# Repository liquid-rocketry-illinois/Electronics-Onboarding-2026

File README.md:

# LRI Electronics Onboarding 2026

This repository is still under construction.

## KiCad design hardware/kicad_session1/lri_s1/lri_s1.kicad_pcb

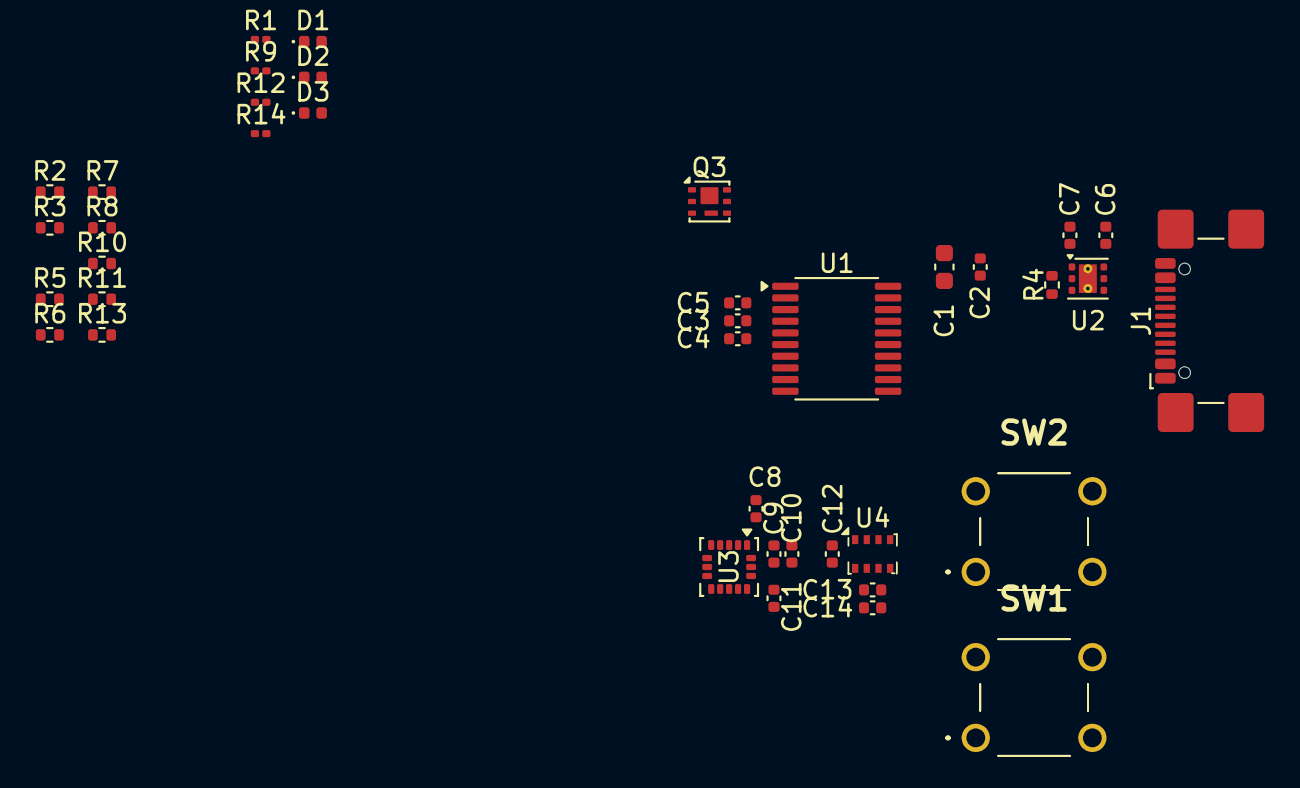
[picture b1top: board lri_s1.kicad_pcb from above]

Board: 2 copper layers, 43 parts (0 on the bottom side), 22 nets, no tracks yet.

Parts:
C1: 4.7u; C_0603_1608Metric
C2, C5, C8, C9, C11, C12, C13: 100n; C_0402_1005Metric
C3, C6, C7: 1u; C_0402_1005Metric
C4: 10n; C_0402_1005Metric
C10, C14: 2.2u; C_0402_1005Metric
D1: GREEN; LED_0402_1005Metric
D2: BLUE; LED_0402_1005Metric
D3: RED; LED_0402_1005Metric
H1, H2, H3, H4: MountingHole; MountingHole_3.2mm_M3
J1: USB_C_Receptacle_USB2.0_16P; USB_C_Receptacle_GCT_USB4110
Q3: CSD17318Q2; Texas_DQK
R1, R9, R12, R14: 10k; R_0201_0603Metric
R2, R3, R4: 5.1k; R_0402_1005Metric
R5, R6, R7: 1k; R_0402_1005Metric
R8, R10, R11, R13: 100; R_0402_1005Metric
SW1, SW2: MJTP1230
U1: STM32F042F6P6; TSSOP-20_4.4x6.5mm_P0.65mm
U2: LP5912-3.3DRV; WSON-6-1EP_2x2mm_P0.65mm_EP1x1.6mm_ThermalVias
U3: ICM-20602; LGA-16_3x3mm_P0.5mm_LayoutBorder3x5y
U4: BMP280; Bosch_LGA-8_2x2.5mm_P0.65mm_ClockwisePinNumbering

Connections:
+3V3: C1.2, C2.2, C3.1, C4.1, C5.2, C7.1, C8.2, C9.2, C10.2, C12.2, C13.2, C14.2, R1.1, R4.1, R5.2, SW1.3 (K), SW1.4 (A), U1.1 (PB8), U1.4 (NRST), U1.5 (VDDA), U1.16 (VDD), U2.1 (OUT), U3.1 (VDDIO), U3.16 (VDD), U4.6 (VDDIO), U4.8 (VDD)
/BMP_~CS: U1.10 (PA4), U4.2 (CSB)
/ICM_~CS: U1.9 (PA3), U3.5 (~CS)
/MCU_LED: R11.2, U1.6 (PA0)
/MCU_PY1: R8.2, R13.2, U1.7 (PA1)
/SPI1_MISO: U1.12 (PA6), U3.4 (SAO/SD0), U4.4 (SCK)
/SPI1_MOSI: U1.11 (PA5), U3.3 (SDA/SDI), U4.3 (SDI)
/SPI1_SCK: U1.13 (PA7), U3.2 (SCL/SPC), U4.5 (SDO)
/USB_D+: J1.A6 (D+), J1.B6 (D+), U1.18 (PA10/PA12)
/USB_D-: J1.A7 (D-), J1.B7 (D-), U1.17 (PA9/PA11)
GND: C1.1, C2.1, C3.2, C4.2, C5.1, C6.2, C7.2, C8.1, C9.1, C10.1, C11.2, C12.1, C13.1, C14.1, D1.1 (K), D2.1 (K), D3.1 (K), J1.A1 (GND), J1.A12 (GND), J1.B1 (GND), J1.B12 (GND), Q3.4 (S), Q3.7 (S), R2.2, R3.2, R9.1, R12.1, R14.1, SW1.1, SW1.2, SW2.1, SW2.2, U1.15 (VSSA), U2.5 (GND), U3.8 (FSYNC), U3.9 (GND), U3.10 (GND), U3.11 (GND), U3.12 (GND), U3.13 (GND), U3.15 (GND), U4.1 (GND), U4.7 (GND)
unnamed: D1.2 (A), R5.1
unnamed: J1.A5 (CC1), R2.1
unnamed: J1.B5 (CC2), R3.1
unnamed: R11.1, R12.2
unnamed: R13.1, R14.2
unnamed: Q3.1 (D), Q3.2 (D), Q3.5 (D), Q3.6 (D), Q3.8 (D), R10.2
unnamed: Q3.3 (G), R8.1, R9.2
unnamed: R1.2, SW2.3 (K), SW2.4 (A)
unnamed: R4.2, U2.3 (PG)
unnamed: C11.1, U3.14 (REGOUT)
VBUS: C6.1, J1.A4 (VBUS), J1.A9 (VBUS), J1.B4 (VBUS), J1.B9 (VBUS), R6.2, R7.2, U2.4 (EN), U2.6 (IN)

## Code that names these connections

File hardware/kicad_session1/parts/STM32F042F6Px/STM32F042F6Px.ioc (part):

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Mcu.Name=STM32F042F6Px
Mcu.Package=TSSOP20
Mcu.UserName=STM32F042F6Px
PA0.Signal=GPIO_Output
PA1.Signal=GPIO_Output
PA2.Signal=GPIO_Output
PA3.Signal=GPIO_Output
PA4.Signal=GPIO_Output
PA5.Mode=Full_Duplex_Master
PA5.Signal=SPI1_SCK
PA6.Mode=Full_Duplex_Master
PA6.Signal=SPI1_MISO
PA7.Mode=Full_Duplex_Master
PA7.Signal=SPI1_MOSI
PB8.Mode=I2C
PB8.Signal=I2C1_SCL
PF0-OSC_IN.Mode=I2C
PF0-OSC_IN.Signal=I2C1_SDA
board=custom

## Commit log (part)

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2026-06-21 session 1 project code
2026-06-21 fixed slides link
